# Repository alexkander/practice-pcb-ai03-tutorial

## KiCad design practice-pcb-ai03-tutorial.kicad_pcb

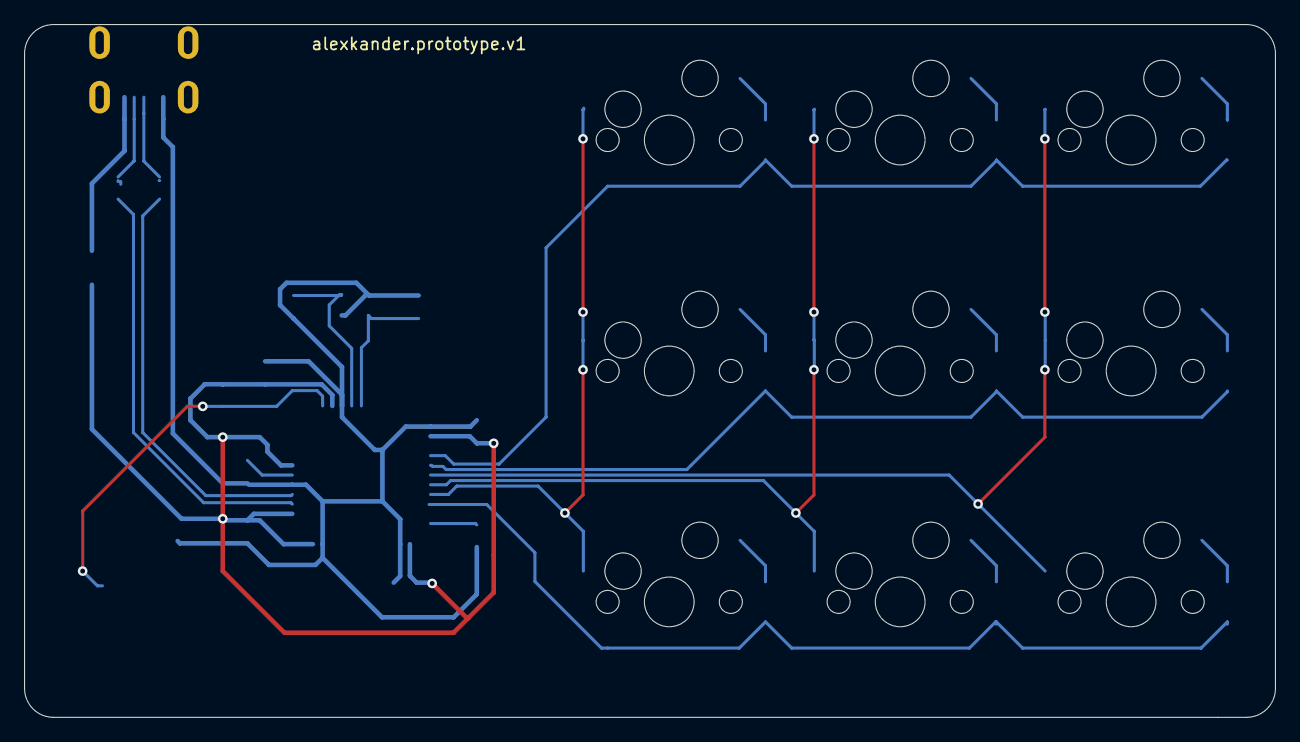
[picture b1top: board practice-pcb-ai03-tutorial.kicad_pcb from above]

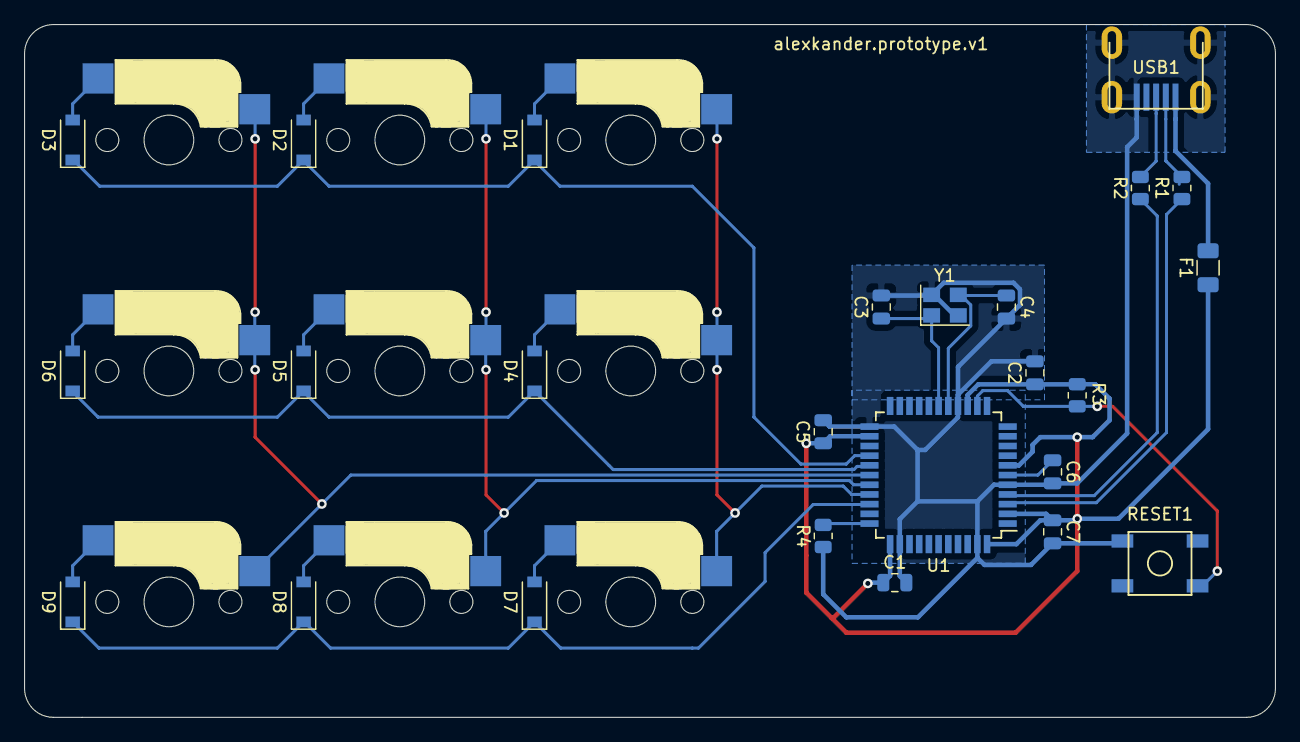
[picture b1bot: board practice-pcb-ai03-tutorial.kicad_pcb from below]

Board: 2 copper layers, 103.2 x 57.2 mm, 34 parts (25 on the bottom side), 27 nets.

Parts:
C1, C2, C5: 0.1uF; C_0805_2012Metric
C3, C4: 22pF; C_0805_2012Metric
C6: 1uF; C_0805_2012Metric
C7: 10uF; C_0805_2012Metric
D1, D2, D3, D4, D5, D6, D7, D8, D9: SOD-123; D_SOD-123
F1: 500mA; Fuse_1206_3216Metric
R1, R2: 22; R_0805_2012Metric
R3, R4: 10k; R_0805_2012Metric
RESET1: SW_Push; SKQG-1155865
SW1, SW2, SW3, SW4, SW5, SW6, SW7, SW8, SW9: MX-NoLED; CherryMX_Hotswap
U1: ATmega32U4-AU; TQFP-44_10x10mm_P0.8mm
USB1: Molex-0548190589
Y1: 16MHz; Crystal_SMD_3225-4Pin_3.2x2.5mm

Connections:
+5V: C1.1, C2.1, C5.1, C7.1, F1.1, R3.1, U1.2, U1.7, U1.14, U1.24, U1.34, U1.44
COL0: SW1.1, SW4.1, SW7.1, U1.30
COL1: SW2.1, SW5.1, SW8.1, U1.29
COL2: SW3.1, SW6.1, SW9.1, U1.28
D+: R2.2, USB1.3
D-: R1.2, USB1.4
GND: C1.2, C2.2, C3.2, C4.2, C5.2, C6.2, C7.2, R4.1, RESET1.1, U1.5, U1.15, U1.23, U1.35, U1.43, USB1.1, USB1.6, Y1.2, Y1.4
unnamed: C3.1, U1.17, Y1.1
unnamed: C4.1, U1.16, Y1.3
unnamed: C6.1, U1.6
unnamed: D1.2, SW1.2
unnamed: D2.2, SW2.2
unnamed: D3.2, SW3.2
unnamed: D4.2, SW4.2
unnamed: D5.2, SW5.2
unnamed: D6.2, SW6.2
unnamed: D7.2, SW7.2
unnamed: D8.2, SW8.2
unnamed: D9.2, SW9.2
unnamed: R1.1, U1.3
unnamed: R2.1, U1.4
unnamed: R3.2, RESET1.2, U1.13
unnamed: R4.2, U1.33
ROW0: D1.1, D2.1, D3.1, U1.26
ROW1: D4.1, D5.1, D6.1, U1.27
ROW2: D7.1, D8.1, D9.1, U1.31
VCC: F1.2, USB1.5

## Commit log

2021-06-13 chore: initial commit
2021-06-13 chore: add libraries submodules
2021-06-13 chore: agrega librerias
2021-06-14 feat: add schematic design
2021-06-15 feat: add board design
2021-06-16 chore(pcb): add hotswap socket for switches
2021-08-24 cambios
